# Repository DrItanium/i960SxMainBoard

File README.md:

This is the kicad project for my basic i960Sx mainboard

This is the culmination of many different designs with the most prominent being
the flattening of my internal modular board design. It was made up of mega2560
shield form factors and nucleo-144 form factor boards. It allowed me to mix and
match ideas without having to fully lay everything out over and over again. I
have no plans of releasing those designs publically because they are not
useful to anyone but myself.

This is a mini-itx board that requires a separate MightyCore development board
to plug into. This board is the culmination of years of work and design. I am
nowhere done but this is the next phase of the design

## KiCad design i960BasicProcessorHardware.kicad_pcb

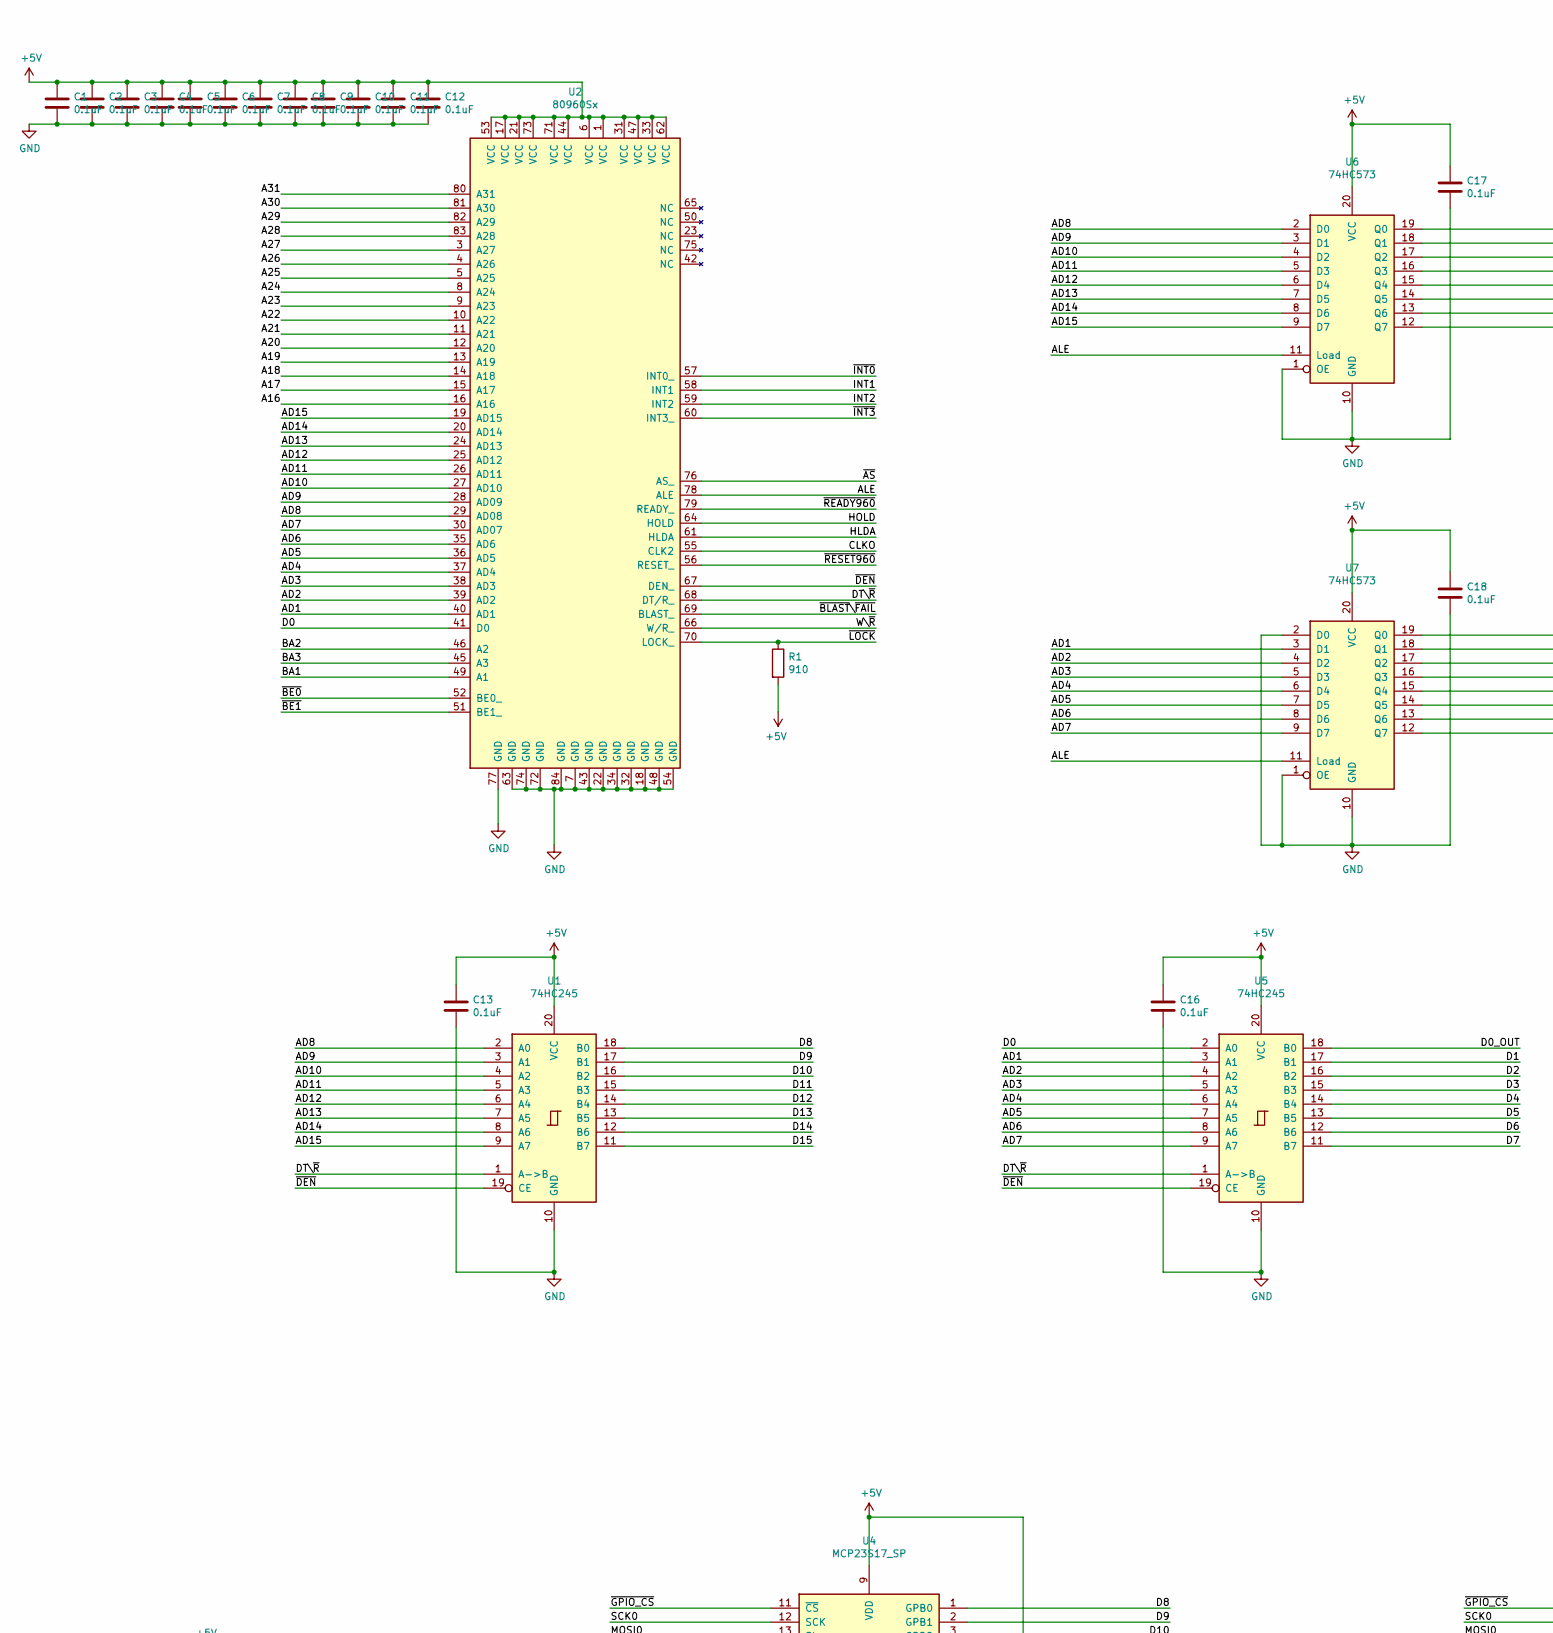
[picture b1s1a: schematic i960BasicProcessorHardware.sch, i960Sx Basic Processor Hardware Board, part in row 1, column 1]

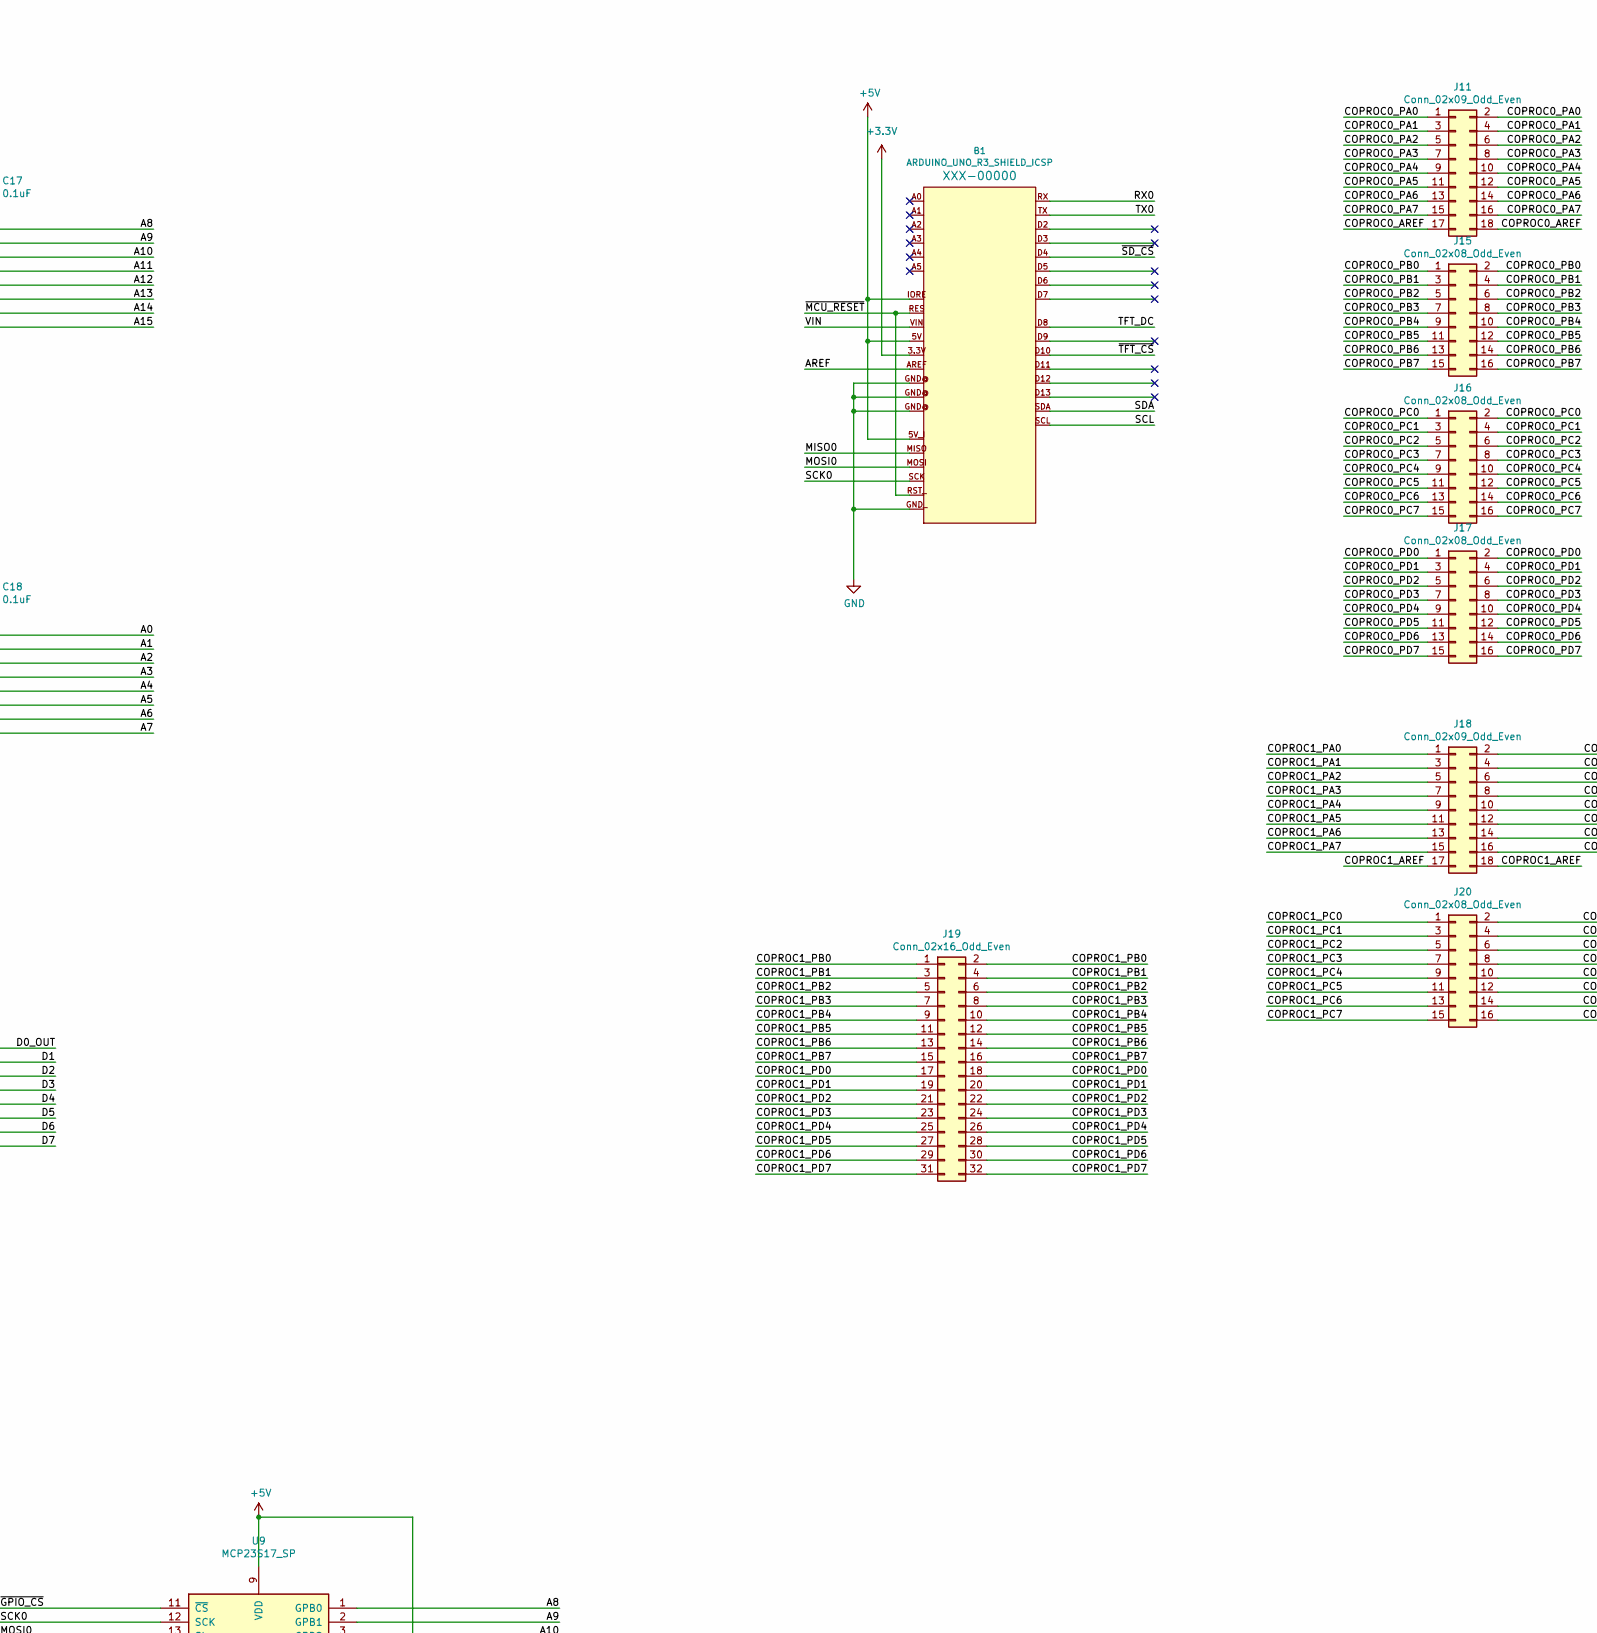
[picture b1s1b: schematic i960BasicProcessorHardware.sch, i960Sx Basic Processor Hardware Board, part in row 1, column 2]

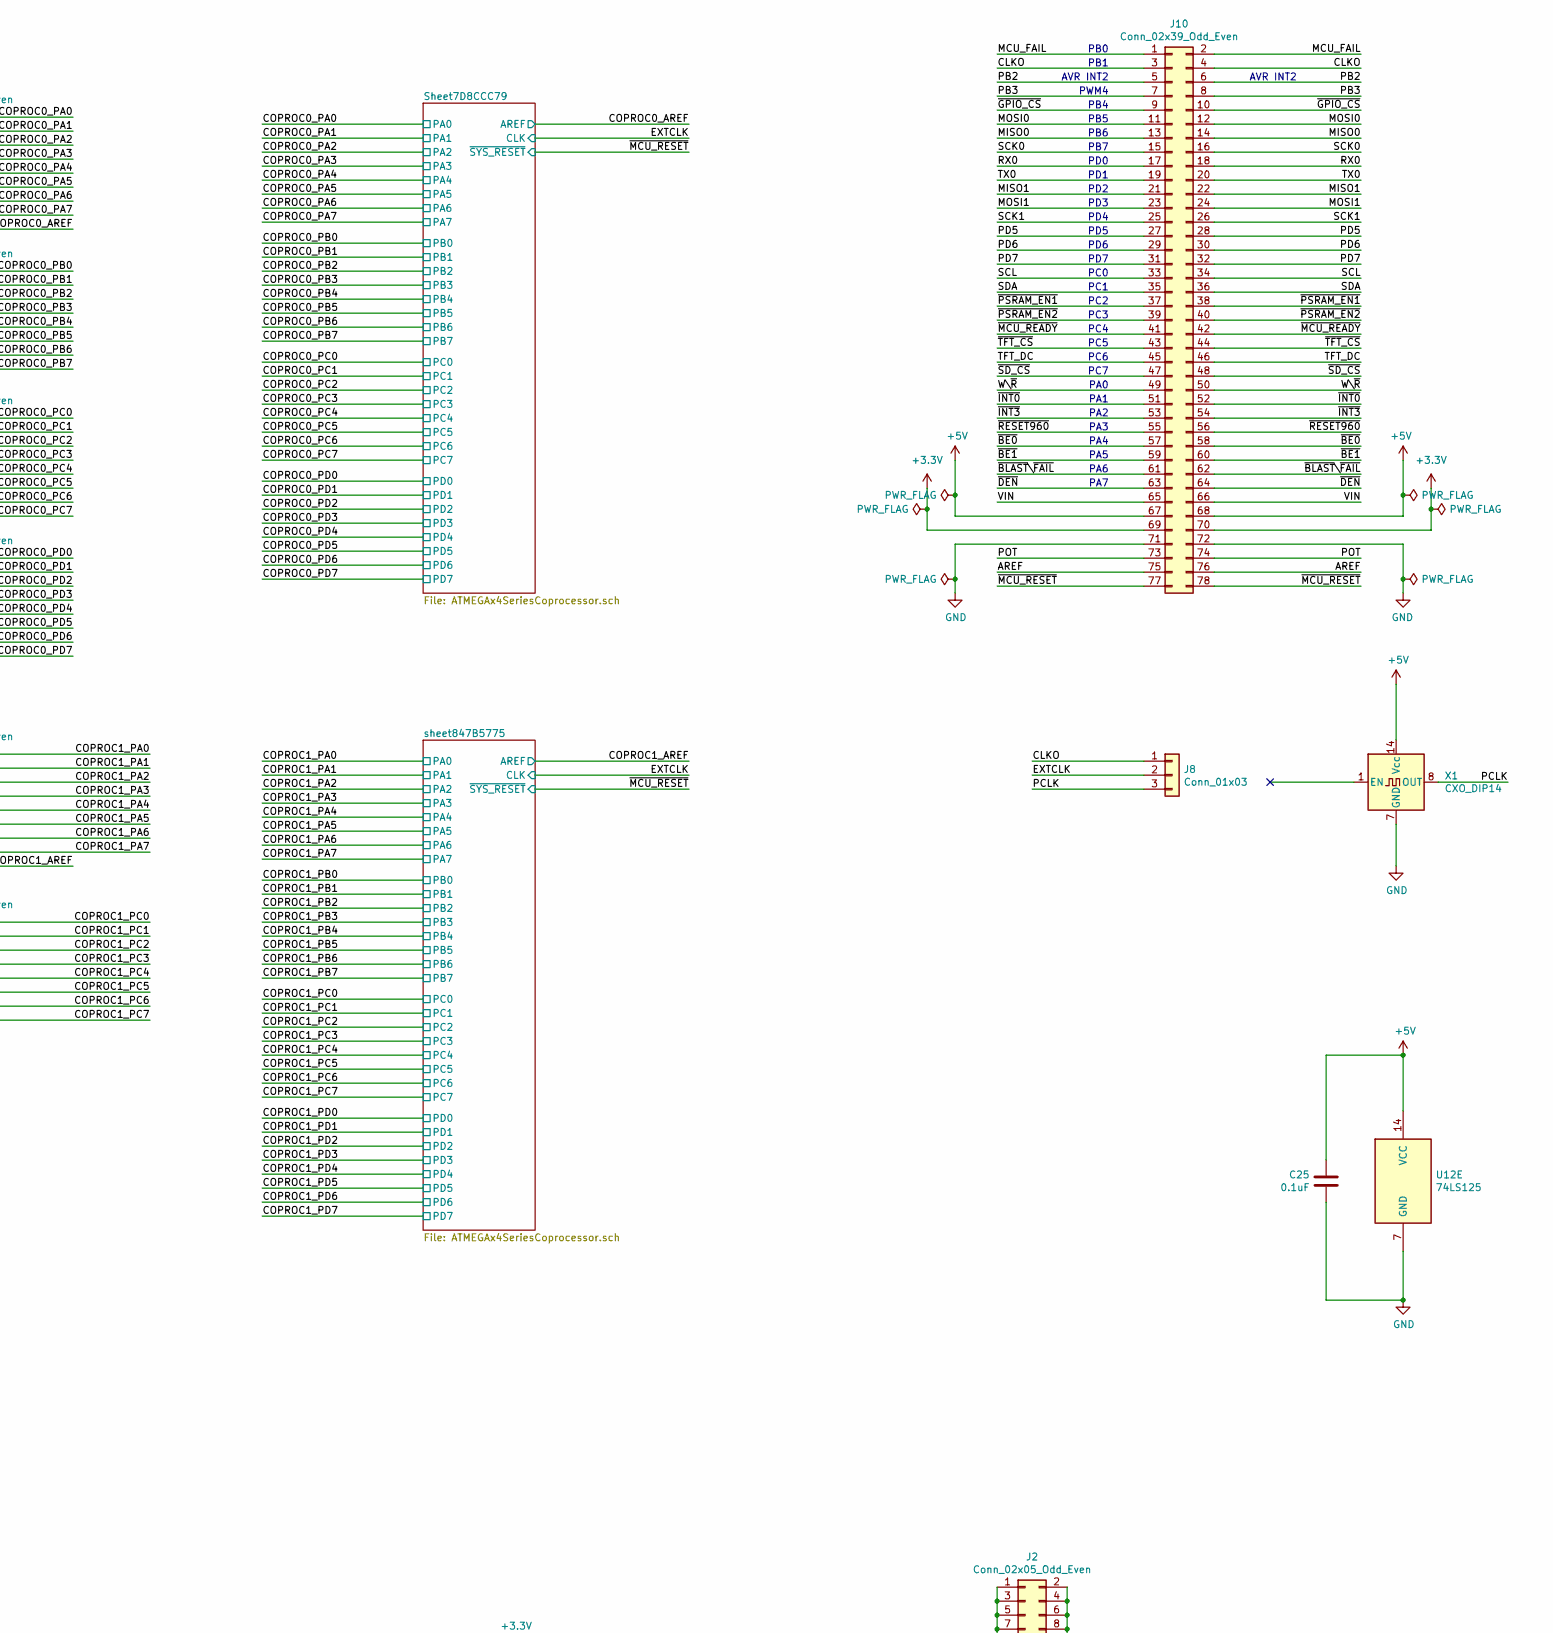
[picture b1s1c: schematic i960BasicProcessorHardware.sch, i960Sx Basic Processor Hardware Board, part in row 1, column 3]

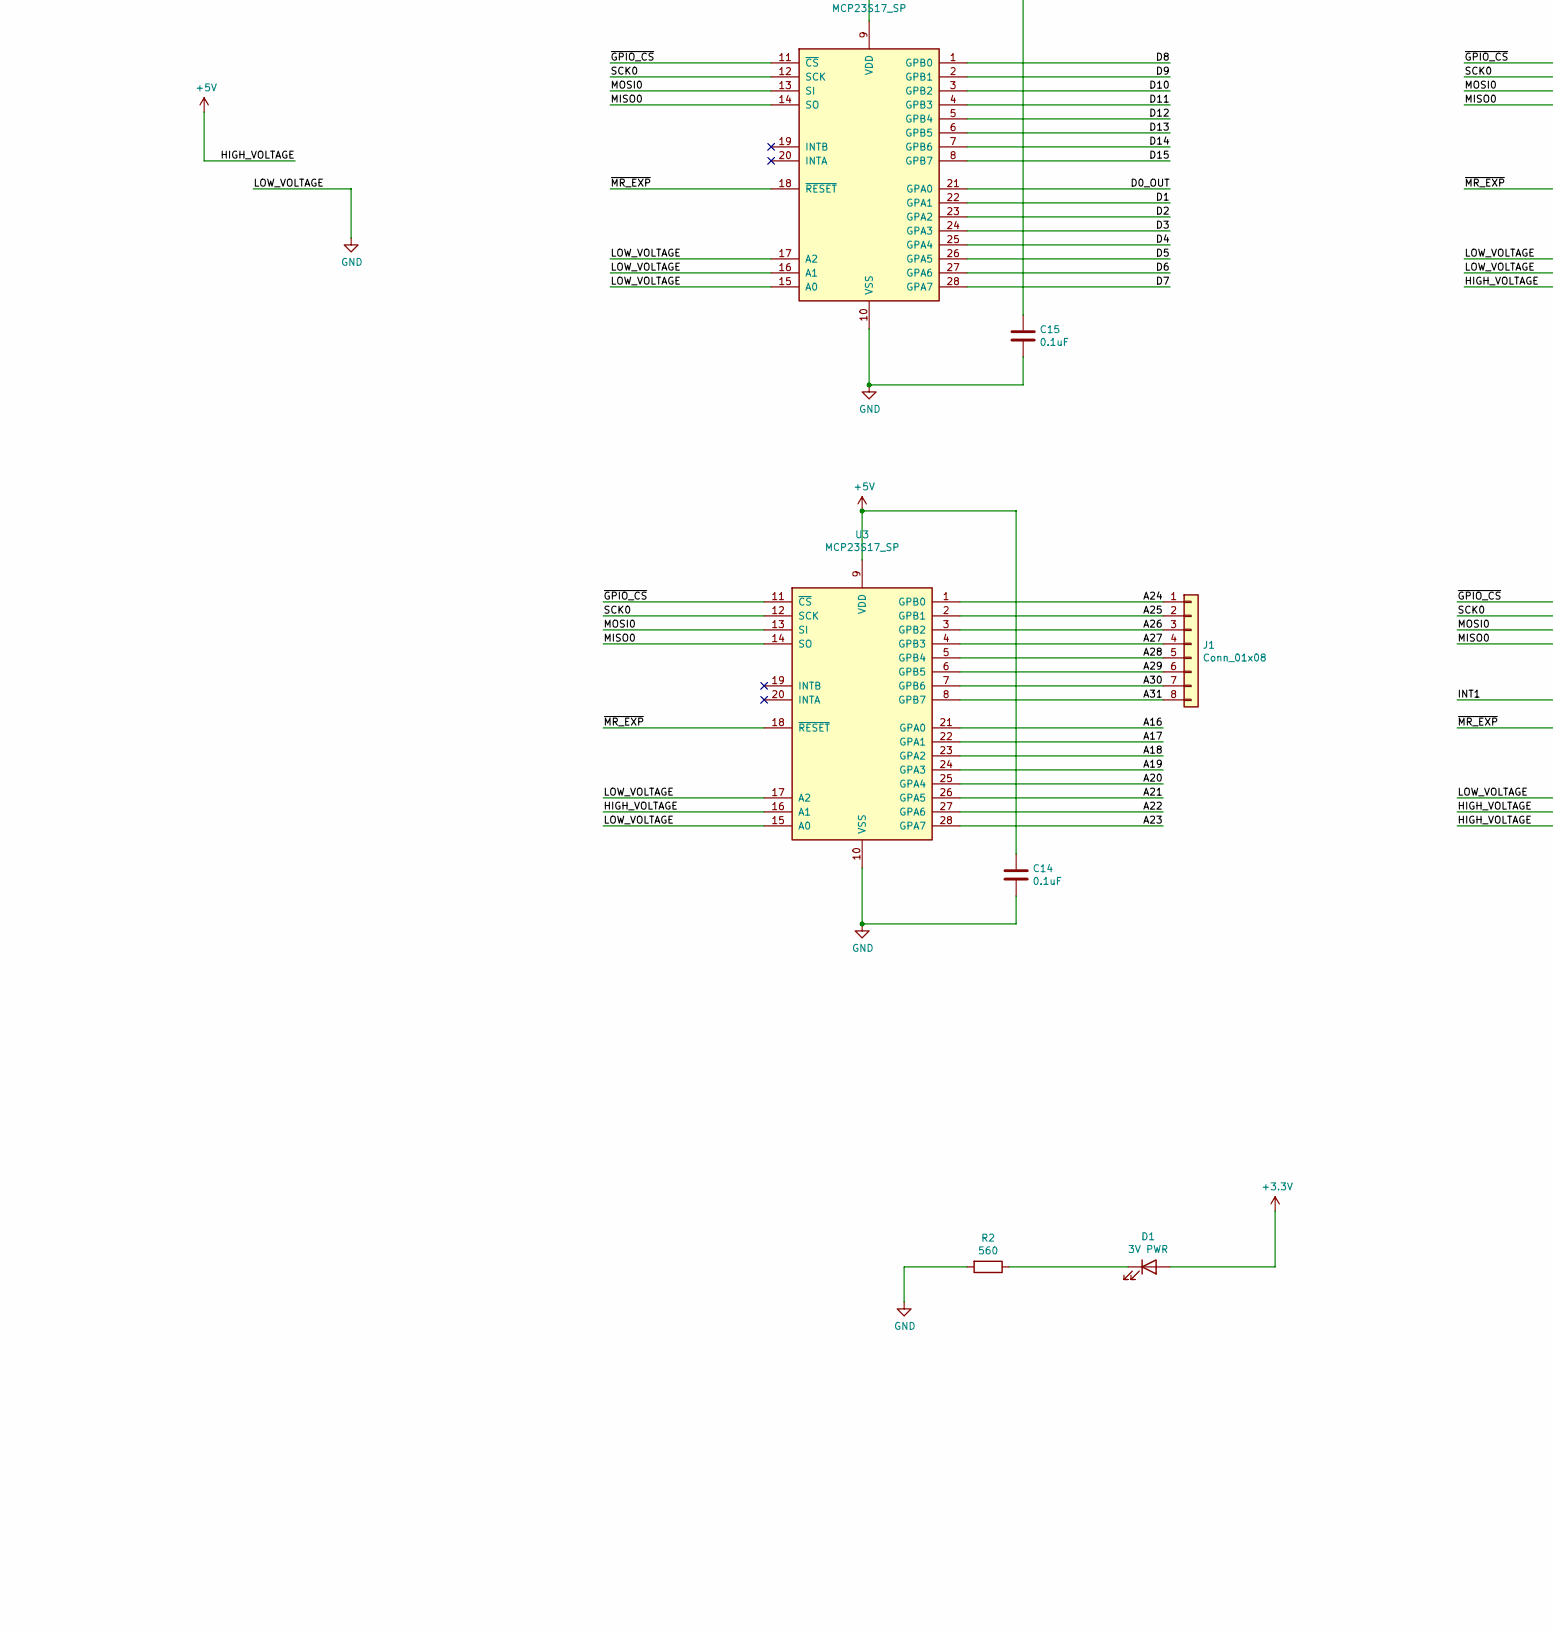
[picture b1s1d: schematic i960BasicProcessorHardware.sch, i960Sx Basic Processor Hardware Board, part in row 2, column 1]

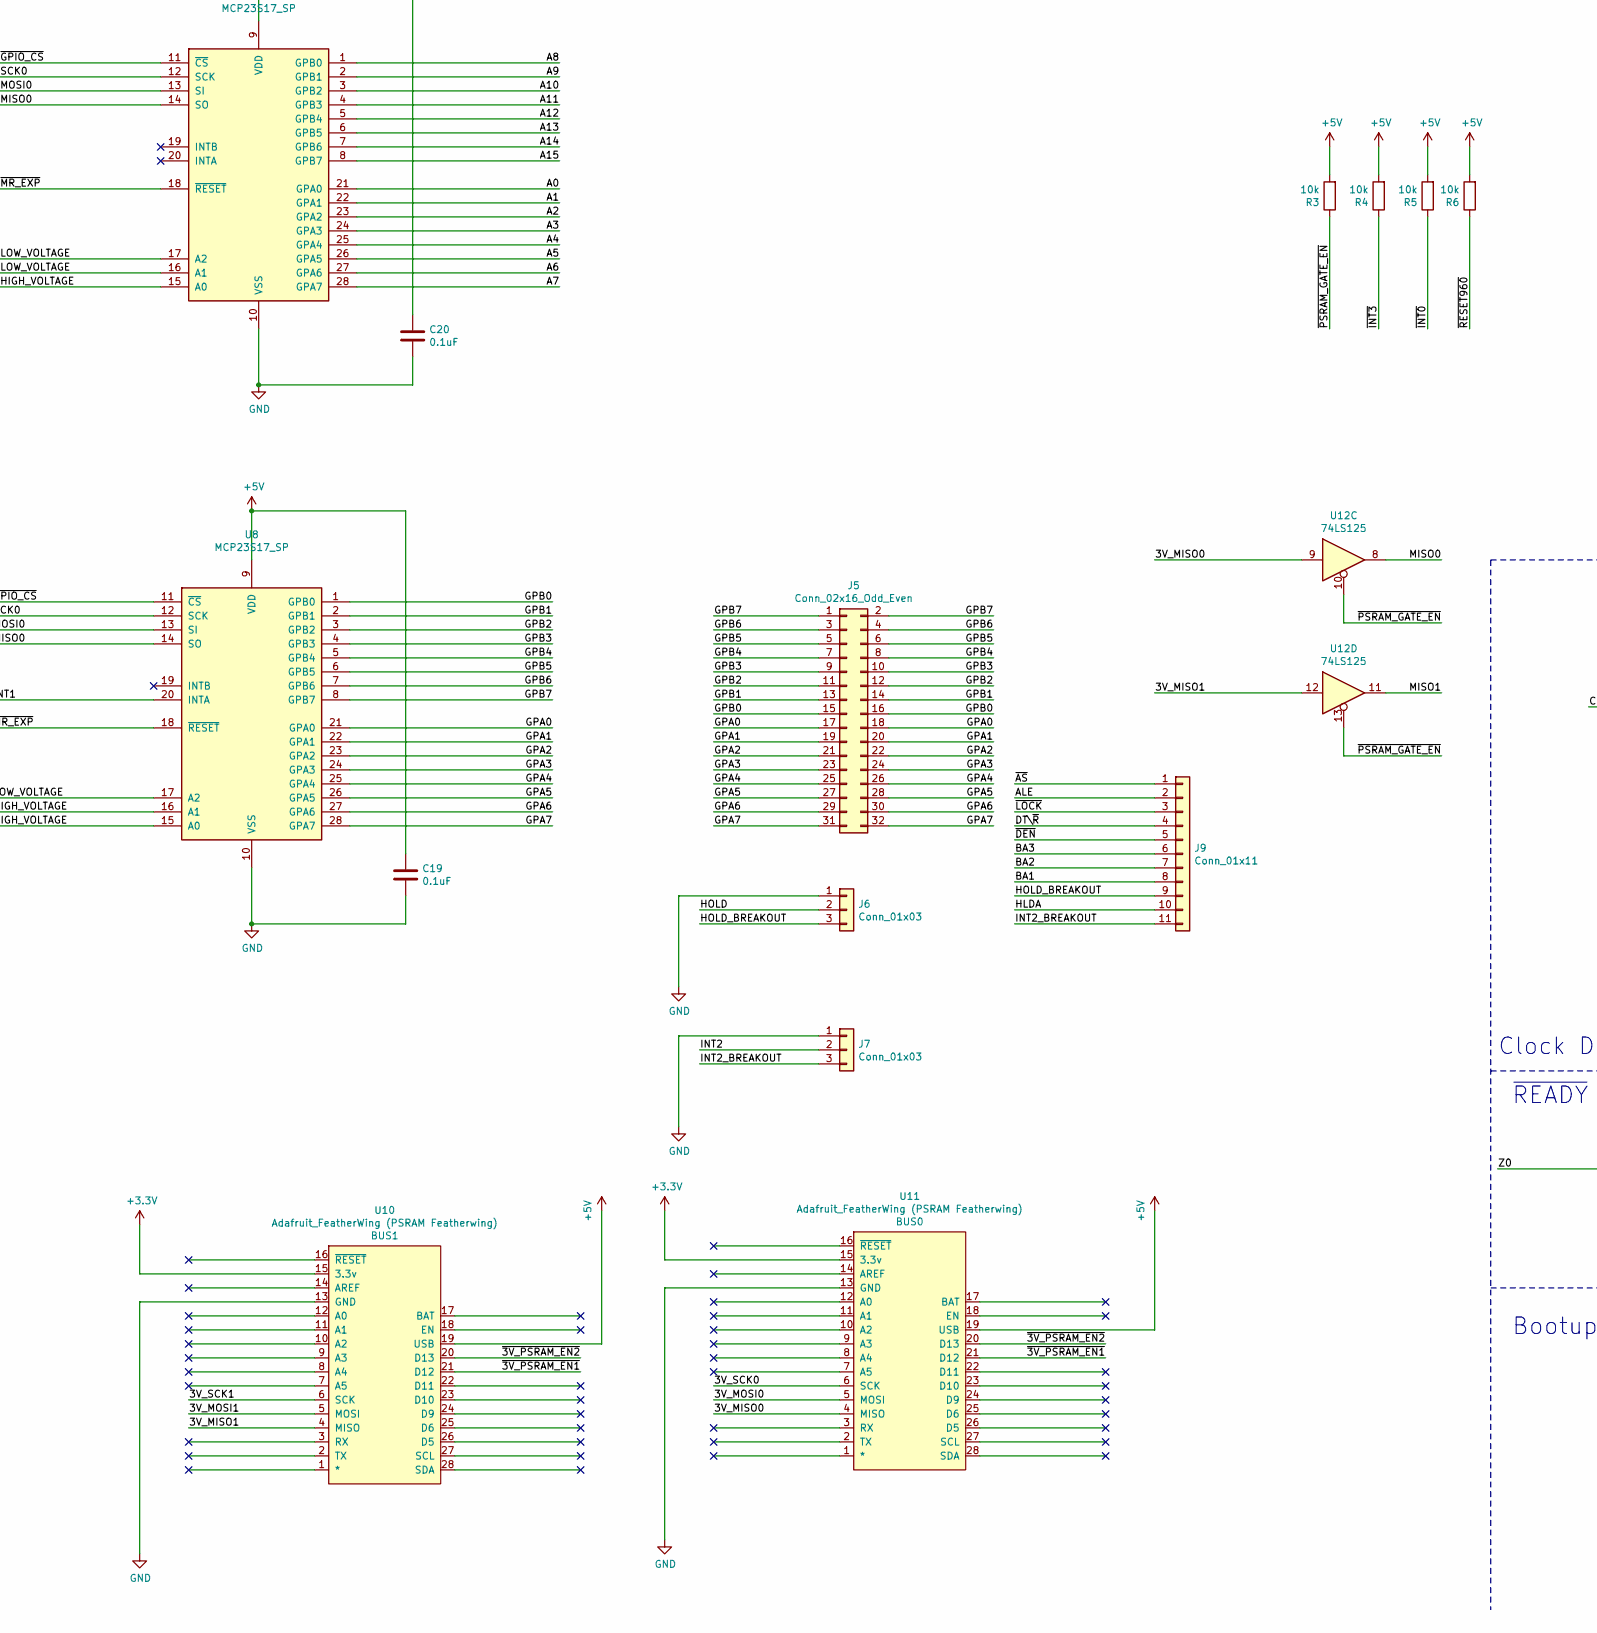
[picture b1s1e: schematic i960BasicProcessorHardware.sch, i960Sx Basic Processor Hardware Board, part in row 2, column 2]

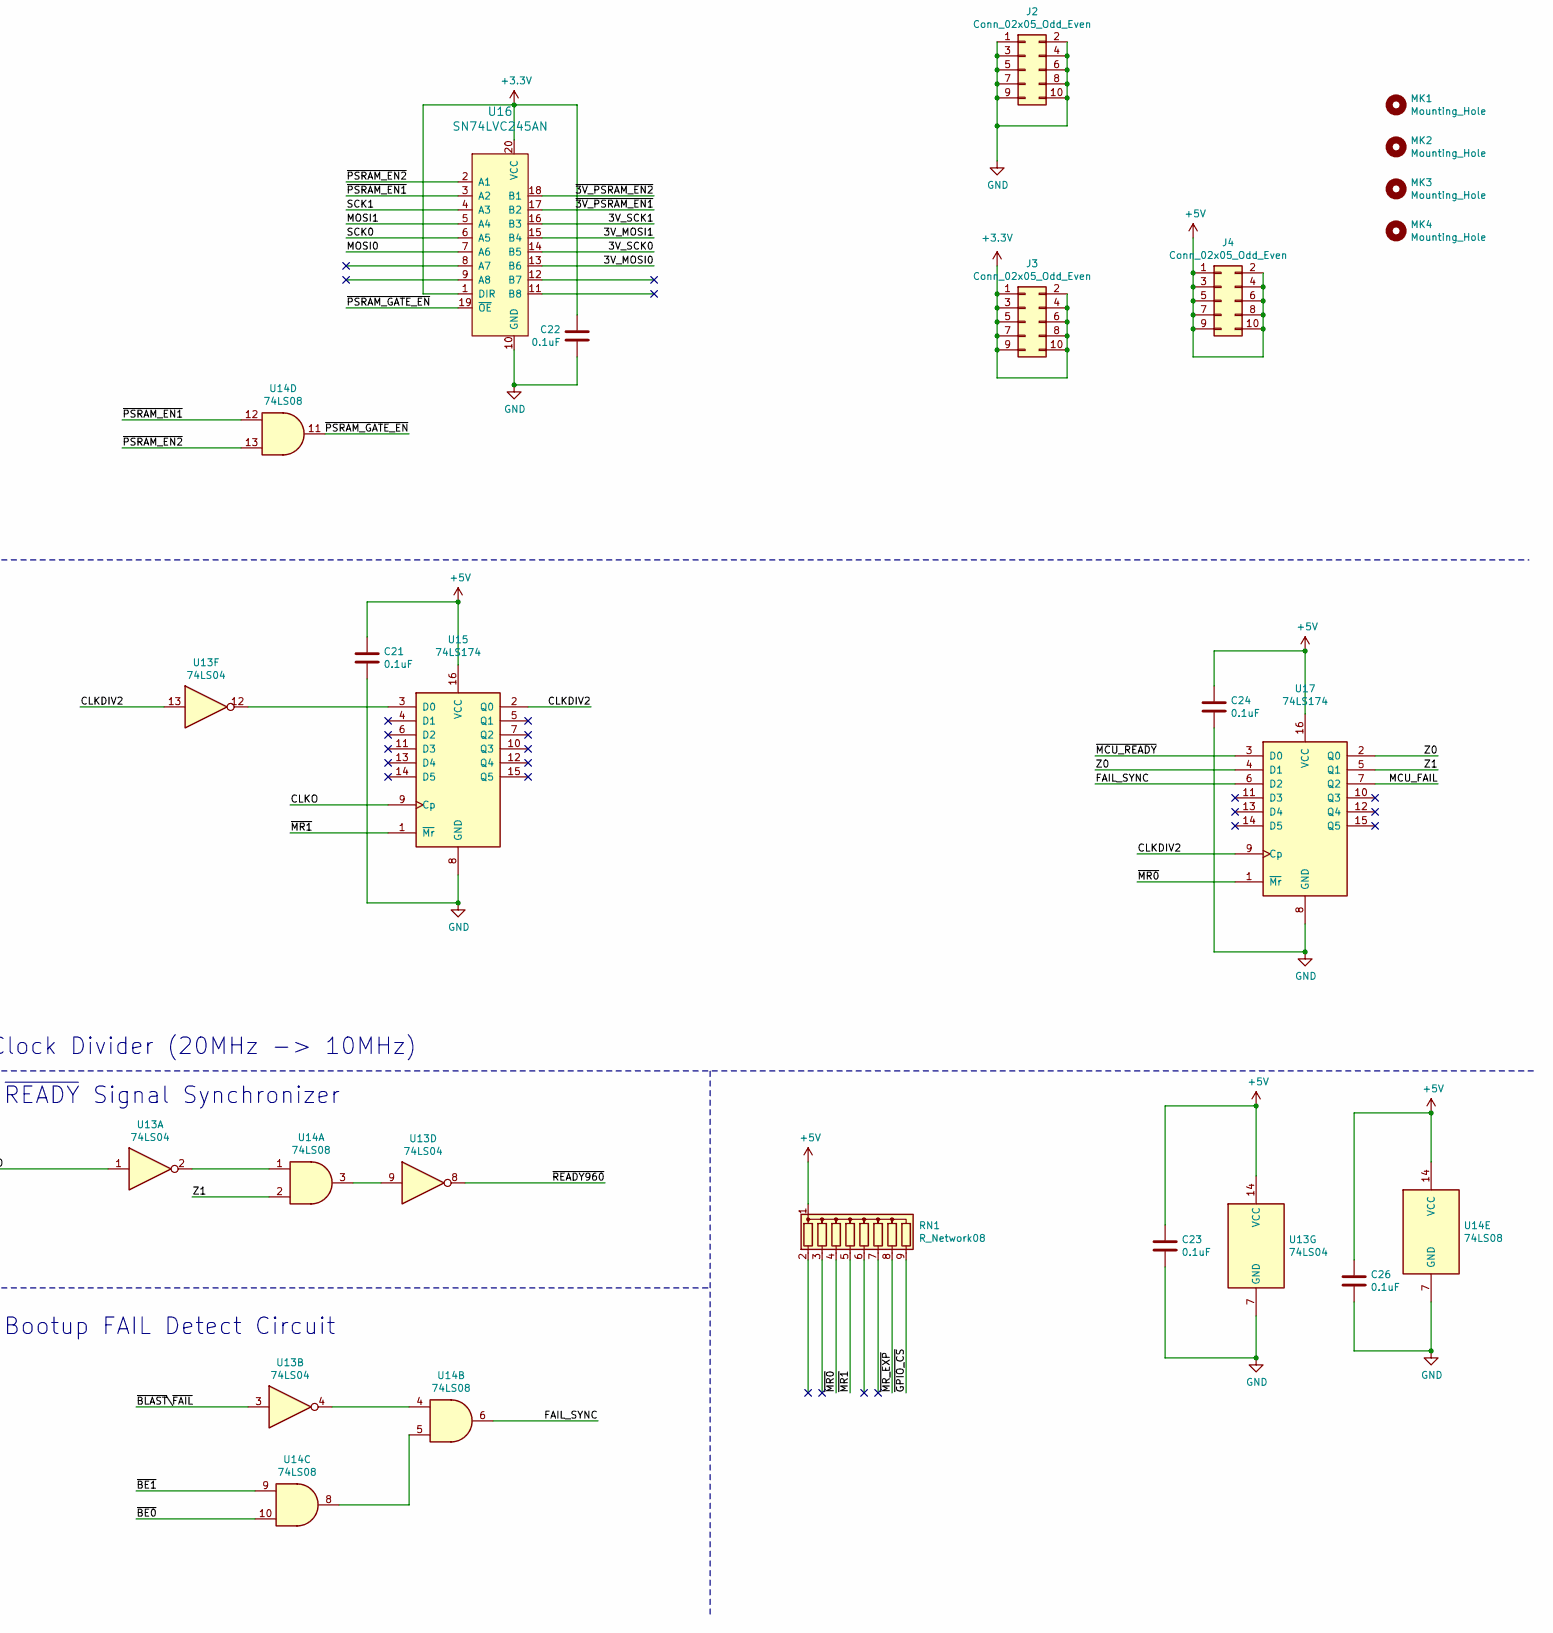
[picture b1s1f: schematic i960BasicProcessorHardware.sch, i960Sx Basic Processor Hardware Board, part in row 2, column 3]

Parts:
B1: ARDUINO_UNO_R3_SHIELD_ICSP; UNO_R3_SHIELD_ICSP
C1, C2, C3, C4, C5, C6, C7, C8, C9, C10, C11, C12, C13, C14, C15, C16, C17, C18, C19, C20, C21, C22, C23, C24, C25, C26: 0.1uF; C_0805_2012Metric_Pad1.18x1.45mm_HandSolder
D1: 3V PWR; LED_0805_2012Metric_Pad1.15x1.40mm_HandSolder
J1: Conn_01x08; PinHeader_1x08_P2.54mm_Vertical
J2, J3, J4: Conn_02x05_Odd_Even; PinHeader_2x05_P2.54mm_Vertical
J5, J19: Conn_02x16_Odd_Even; PinHeader_2x16_P2.54mm_Vertical
J6, J7, J8: Conn_01x03; PinHeader_1x03_P2.54mm_Vertical
J9: Conn_01x11; PinHeader_1x11_P2.54mm_Vertical
J10: Conn_02x39_Odd_Even; PinHeader_2x39_P2.54mm_Vertical
J11, J18: Conn_02x09_Odd_Even; PinHeader_2x09_P2.54mm_Vertical
J15, J16, J17, J20: Conn_02x08_Odd_Even; PinHeader_2x08_P2.54mm_Vertical
MK1, MK2, MK3, MK4: Mounting_Hole; MountingHole_4.3mm_M4
R1: 910; R_0805_2012Metric_Pad1.20x1.40mm_HandSolder
R2: 560; R_0805_2012Metric_Pad1.20x1.40mm_HandSolder
R3, R4, R5, R6: 10k; R_0805_2012Metric_Pad1.20x1.40mm_HandSolder
RN1: R_Network08; R_Array_SIP9
U1, U5: 74HC245; DIP-20_W7.62mm_Socket
U2: 80960Sx; PLCC-84_THT-Socket
U3, U4, U8, U9: MCP23S17_SP; DIP-28_W7.62mm
U6, U7: 74HC573; DIP-20_W7.62mm_Socket
U10, U11: Adafruit_FeatherWing (PSRAM Featherwing); ADAFRUIT_FEATHER
U12: 74LS125; DIP-14_W7.62mm_Socket
U13: 74LS04; DIP-14_W7.62mm_Socket
U14: 74LS08; DIP-14_W7.62mm_Socket
U15, U17: 74LS174; DIP-16_W7.62mm_Socket
U16: SN74LVC245AN; DIP-20_W7.62mm_Socket; MPN SN74LVC245AN; Digi-Key_PN 296-8503-5-ND
X1: CXO_DIP14; Oscillator_DIP-14

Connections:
+3V3: B1.3.3V, C22.1, D1.2 (A), J3.1, J3.2, J3.3, J3.4, J3.5, J3.6, J3.7, J3.8, J3.9, J3.10, J10.69, J10.70, U10.15 (3.3v), U11.15 (3.3v), U16.1 (DIR), U16.20 (VCC)
+5V: B1.5V, B1.5V_I (VCC), B1.IORE (IOREF), C1.1, C2.1, C3.1, C4.1, C5.1, C6.1, C7.1, C8.1, C9.1, C10.1, C11.1, C12.1, C13.1, C14.1, C15.1, C16.1, C17.1, C18.1, C19.1, C20.1, C21.1, C23.1, C24.1, C25.1, C26.1, J4.1, J4.2, J4.3, J4.4, J4.5, J4.6, J4.7, J4.8, J4.9, J4.10, J10.67, J10.68, R1.2, R3.2, R4.2, R5.2, R6.2, RN1.1 (common), U1.20 (VCC), U2.1 (VCC), U2.6 (VCC), U2.17 (VCC), U2.21 (VCC), U2.31 (VCC), U2.33 (VCC), U2.44 (VCC), U2.47 (VCC), U2.53 (VCC), U2.62 (VCC), U2.71 (VCC), U2.73 (VCC), U3.9 (VDD), U3.16 (A1), U4.9 (VDD), U5.20 (VCC), U6.20 (VCC), U7.20 (VCC), U8.9 (VDD), U8.15 (A0), U8.16 (A1), U9.9 (VDD), U9.15 (A0), U10.19 (USB), U11.19 (USB), U12.14 (VCC), U13.14 (VCC), U14.14 (VCC), U15.16 (VCC), U17.16 (VCC), X1.14 (Vcc); also elsewhere on the board
/3V_MISO0: U11.4 (MISO), U12.9
/3V_MISO1: U10.4 (MISO), U12.12
/3V_MOSI0: U11.5 (MOSI), U16.13 (B6)
/3V_MOSI1: U10.5 (MOSI), U16.15 (B4)
/3V_SCK0: U11.6 (SCK), U16.14 (B5)
/3V_SCK1: U10.6 (SCK), U16.16 (B3)
/A0: U7.19 (Q0), U9.21 (GPA0)
/A1: U7.18 (Q1), U9.22 (GPA1)
/A2: U7.17 (Q2), U9.23 (GPA2)
/A3: U7.16 (Q3), U9.24 (GPA3)
/A4: U7.15 (Q4), U9.25 (GPA4)
/A5: U7.14 (Q5), U9.26 (GPA5)
/A6: U7.13 (Q6), U9.27 (GPA6)
/A7: U7.12 (Q7), U9.28 (GPA7)
/A8: U6.19 (Q0), U9.1 (GPB0)
/A9: U6.18 (Q1), U9.2 (GPB1)
/A10: U6.17 (Q2), U9.3 (GPB2)
/A11: U6.16 (Q3), U9.4 (GPB3)
/A12: U6.15 (Q4), U9.5 (GPB4)
/A13: U6.14 (Q5), U9.6 (GPB5)
/A14: U6.13 (Q6), U9.7 (GPB6)
/A15: U6.12 (Q7), U9.8 (GPB7)
/A16: U2.16 (A16), U3.21 (GPA0)
/A17: U2.15 (A17), U3.22 (GPA1)
/A18: U2.14 (A18), U3.23 (GPA2)
/A19: U2.13 (A19), U3.24 (GPA3)
/A20: U2.12 (A20), U3.25 (GPA4)
/A21: U2.11 (A21), U3.26 (GPA5)
/A22: U2.10 (A22), U3.27 (GPA6)
/A23: U2.9 (A23), U3.28 (GPA7)
/A24: J1.1, U2.8 (A24), U3.1 (GPB0)
/A25: J1.2, U2.5 (A25), U3.2 (GPB1)
/A26: J1.3, U2.4 (A26), U3.3 (GPB2)
/A27: J1.4, U2.3 (A27), U3.4 (GPB3)
/A28: J1.5, U2.83 (A28), U3.5 (GPB4)
/A29: J1.6, U2.82 (A29), U3.6 (GPB5)
/A30: J1.7, U2.81 (A30), U3.7 (GPB6)
/A31: J1.8, U2.80 (A31), U3.8 (GPB7)
/AD1: U2.40 (AD1), U5.3 (A1), U7.3 (D1)
/AD2: U2.39 (AD2), U5.4 (A2), U7.4 (D2)
/AD3: U2.38 (AD3), U5.5 (A3), U7.5 (D3)
/AD4: U2.37 (AD4), U5.6 (A4), U7.6 (D4)
/AD5: U2.36 (AD5), U5.7 (A5), U7.7 (D5)
/AD6: U2.35 (AD6), U5.8 (A6), U7.8 (D6)
/AD7: U2.30 (AD07), U5.9 (A7), U7.9 (D7)
/AD8: U1.2 (A0), U2.29 (AD08), U6.2 (D0)
/AD9: U1.3 (A1), U2.28 (AD09), U6.3 (D1)
/AD10: U1.4 (A2), U2.27 (AD10), U6.4 (D2)
/AD11: U1.5 (A3), U2.26 (AD11), U6.5 (D3)
/AD12: U1.6 (A4), U2.25 (AD12), U6.6 (D4)
/AD13: U1.7 (A5), U2.24 (AD13), U6.7 (D5)
/AD14: U1.8 (A6), U2.20 (AD14), U6.8 (D6)
/AD15: U1.9 (A7), U2.19 (AD15), U6.9 (D7)
/ALE: J9.2, U2.78 (ALE), U6.11 (Load), U7.11 (Load)
/AREF: B1.AREF, J10.75, J10.76
/BA1: J9.8, U2.49 (A1)
/BA2: J9.7, U2.46 (A2)
/BA3: J9.6, U2.45 (A3)
/CLKDIV2: U13.13, U15.2 (Q0), U17.9 (Cp)
/CLKO: J8.1, J10.3, J10.4, U2.55 (CLK2), U15.9 (Cp)
/COPROC0_AREF: J11.17, J11.18; also elsewhere on the board
/COPROC0_PA0: J11.1, J11.2; also elsewhere on the board
/COPROC0_PA1: J11.3, J11.4; also elsewhere on the board
/COPROC0_PA2: J11.5, J11.6; also elsewhere on the board
/COPROC0_PA3: J11.7, J11.8; also elsewhere on the board
/COPROC0_PA4: J11.9, J11.10; also elsewhere on the board
/COPROC0_PA5: J11.11, J11.12; also elsewhere on the board
/COPROC0_PA6: J11.13, J11.14; also elsewhere on the board
/COPROC0_PA7: J11.15, J11.16; also elsewhere on the board
/COPROC0_PB0: J15.1, J15.2; also elsewhere on the board
/COPROC0_PB1: J15.3, J15.4; also elsewhere on the board
/COPROC0_PB2: J15.5, J15.6; also elsewhere on the board
/COPROC0_PB3: J15.7, J15.8; also elsewhere on the board
/COPROC0_PB4: J15.9, J15.10; also elsewhere on the board
/COPROC0_PB5: J15.11, J15.12; also elsewhere on the board
/COPROC0_PB6: J15.13, J15.14; also elsewhere on the board
/COPROC0_PB7: J15.15, J15.16; also elsewhere on the board
/COPROC0_PC0: J16.1, J16.2; also elsewhere on the board
/COPROC0_PC1: J16.3, J16.4; also elsewhere on the board
/COPROC0_PC2: J16.5, J16.6; also elsewhere on the board
/COPROC0_PC3: J16.7, J16.8; also elsewhere on the board
/COPROC0_PC4: J16.9, J16.10; also elsewhere on the board
/COPROC0_PC5: J16.11, J16.12; also elsewhere on the board
/COPROC0_PC6: J16.13, J16.14; also elsewhere on the board
/COPROC0_PC7: J16.15, J16.16; also elsewhere on the board
/COPROC0_PD0: J17.1, J17.2; also elsewhere on the board
/COPROC0_PD1: J17.3, J17.4; also elsewhere on the board
/COPROC0_PD2: J17.5, J17.6; also elsewhere on the board
/COPROC0_PD3: J17.7, J17.8; also elsewhere on the board
/COPROC0_PD4: J17.9, J17.10; also elsewhere on the board
/COPROC0_PD5: J17.11, J17.12; also elsewhere on the board
/COPROC0_PD6: J17.13, J17.14; also elsewhere on the board
/COPROC0_PD7: J17.15, J17.16; also elsewhere on the board
/COPROC1_AREF: J18.17, J18.18; also elsewhere on the board
/COPROC1_PA0: J18.1, J18.2; also elsewhere on the board
/COPROC1_PA1: J18.3, J18.4; also elsewhere on the board
/COPROC1_PA2: J18.5, J18.6; also elsewhere on the board
/COPROC1_PA3: J18.7, J18.8; also elsewhere on the board
/COPROC1_PA4: J18.9, J18.10; also elsewhere on the board
/COPROC1_PA5: J18.11, J18.12; also elsewhere on the board
/COPROC1_PA6: J18.13, J18.14; also elsewhere on the board
/COPROC1_PA7: J18.15, J18.16; also elsewhere on the board
/COPROC1_PB0: J19.1, J19.2; also elsewhere on the board
/COPROC1_PB1: J19.3, J19.4; also elsewhere on the board
/COPROC1_PB2: J19.5, J19.6; also elsewhere on the board
/COPROC1_PB3: J19.7, J19.8; also elsewhere on the board
/COPROC1_PB4: J19.9, J19.10; also elsewhere on the board
/COPROC1_PB5: J19.11, J19.12; also elsewhere on the board
/COPROC1_PB6: J19.13, J19.14; also elsewhere on the board
/COPROC1_PB7: J19.15, J19.16; also elsewhere on the board
/COPROC1_PC0: J20.1, J20.2; also elsewhere on the board
/COPROC1_PC1: J20.3, J20.4; also elsewhere on the board
/COPROC1_PC2: J20.5, J20.6; also elsewhere on the board
/COPROC1_PC3: J20.7, J20.8; also elsewhere on the board
/COPROC1_PC4: J20.9, J20.10; also elsewhere on the board
/COPROC1_PC5: J20.11, J20.12; also elsewhere on the board
/COPROC1_PC6: J20.13, J20.14; also elsewhere on the board
/COPROC1_PC7: J20.15, J20.16; also elsewhere on the board
/COPROC1_PD0: J19.17, J19.18; also elsewhere on the board
/COPROC1_PD1: J19.19, J19.20; also elsewhere on the board
/COPROC1_PD2: J19.21, J19.22; also elsewhere on the board
/COPROC1_PD3: J19.23, J19.24; also elsewhere on the board
/COPROC1_PD4: J19.25, J19.26; also elsewhere on the board
/COPROC1_PD5: J19.27, J19.28; also elsewhere on the board
/COPROC1_PD6: J19.29, J19.30; also elsewhere on the board
/COPROC1_PD7: J19.31, J19.32; also elsewhere on the board
/D0: U2.41 (D0), U5.2 (A0)
/D0_OUT: U4.21 (GPA0), U5.18 (B0)
/D1: U4.22 (GPA1), U5.17 (B1)
/D2: U4.23 (GPA2), U5.16 (B2)
/D3: U4.24 (GPA3), U5.15 (B3)
/D4: U4.25 (GPA4), U5.14 (B4)
/D5: U4.26 (GPA5), U5.13 (B5)
/D6: U4.27 (GPA6), U5.12 (B6)
/D7: U4.28 (GPA7), U5.11 (B7)
/D8: U1.18 (B0), U4.1 (GPB0)
/D9: U1.17 (B1), U4.2 (GPB1)
/D10: U1.16 (B2), U4.3 (GPB2)
/D11: U1.15 (B3), U4.4 (GPB3)
/D12: U1.14 (B4), U4.5 (GPB4)
/D13: U1.13 (B5), U4.6 (GPB5)
/D14: U1.12 (B6), U4.7 (GPB6)
/D15: U1.11 (B7), U4.8 (GPB7)
/DT\~R: J9.4, U1.1 (A->B), U2.68 (DT/R_), U5.1 (A->B)
/EXTCLK: J8.2; also elsewhere on the board
/FAIL_SYNC: U14.6, U17.6 (D2)
/GPA0: J5.17, J5.18, U8.21 (GPA0)
/GPA1: J5.19, J5.20, U8.22 (GPA1)
/GPA2: J5.21, J5.22, U8.23 (GPA2)
/GPA3: J5.23, J5.24, U8.24 (GPA3)
/GPA4: J5.25, J5.26, U8.25 (GPA4)
/GPA5: J5.27, J5.28, U8.26 (GPA5)
/GPA6: J5.29, J5.30, U8.27 (GPA6)
/GPA7: J5.31, J5.32, U8.28 (GPA7)
/GPB0: J5.15, J5.16, U8.1 (GPB0)
/GPB1: J5.13, J5.14, U8.2 (GPB1)
/GPB2: J5.11, J5.12, U8.3 (GPB2)
/GPB3: J5.9, J5.10, U8.4 (GPB3)
/GPB4: J5.7, J5.8, U8.5 (GPB4)
/GPB5: J5.5, J5.6, U8.6 (GPB5)
/GPB6: J5.3, J5.4, U8.7 (GPB6)
/GPB7: J5.1, J5.2, U8.8 (GPB7)
/HLDA: J9.10, U2.61 (HLDA)
/HOLD: J6.2, U2.64 (HOLD)
/HOLD_BREAKOUT: J6.3, J9.9
/INT1: U2.58 (INT1), U8.20 (INTA)
/INT2: J7.2, U2.59 (INT2)
/INT2_BREAKOUT: J7.3, J9.11
/MCU_FAIL: J10.1, J10.2, U17.7 (Q2)
/MISO0: B1.MISO, J10.13, J10.14, U3.14 (SO), U4.14 (SO), U8.14 (SO), U9.14 (SO), U12.8
/MISO1: J10.21, J10.22, U12.11
/MOSI0: B1.MOSI, J10.11, J10.12, U3.13 (SI), U4.13 (SI), U8.13 (SI), U9.13 (SI), U16.7 (A6)
/MOSI1: J10.23, J10.24, U16.5 (A4)
/PB2: J10.5, J10.6
/PB3: J10.7, J10.8
/PCLK: J8.3, X1.8 (OUT)
/PD5: J10.27, J10.28
/PD6: J10.29, J10.30
/PD7: J10.31, J10.32
/POT: J10.73, J10.74
/RX0: B1.RX (D0), J10.17, J10.18
/SCK0: B1.SCK, J10.15, J10.16, U3.12 (SCK), U4.12 (SCK), U8.12 (SCK), U9.12 (SCK), U16.6 (A5)
/SCK1: J10.25, J10.26, U16.4 (A3)
/SCL: B1.SCL, J10.33, J10.34
/SDA: B1.SDA, J10.35, J10.36
/TFT_DC: B1.D8, J10.45, J10.46
/TX0: B1.TX (D1), J10.19, J10.20
/VIN: B1.VIN, J10.65, J10.66
/W\~R~: J10.49, J10.50, U2.66 (W/R_)
/Z0: U13.1, U17.2 (Q0), U17.4 (D1)
/Z1: U14.2, U17.5 (Q1)
/~3V_PSRAM_EN1: U10.21 (D12), U11.21 (D12), U16.17 (B2)
/~3V_PSRAM_EN2: U10.20 (D13), U11.20 (D13), U16.18 (B1)
/~AS: J9.1, U2.76 (AS_)
/~BE0: J10.57, J10.58, U2.52 (BE0_), U14.10
/~BE1: J10.59, J10.60, U2.51 (BE1_), U14.9
/~BLAST~\~FAIL~: J10.61, J10.62, U2.69 (BLAST_), U13.3
/~DEN: J9.5, J10.63, J10.64, U1.19 (CE), U2.67 (DEN_), U5.19 (CE)
/~GPIO_CS: J10.9, J10.10, RN1.9 (R8), U3.11 (~CS~), U4.11 (~CS~), U8.11 (~CS~), U9.11 (~CS~)
/~INT0: J10.51, J10.52, R5.1, U2.57 (INT0_)
/~INT3: J10.53, J10.54, R4.1, U2.60 (INT3_)
/~LOCK: J9.3, R1.1, U2.70 (LOCK_)
/~MCU_READY: J10.41, J10.42, U17.3 (D0)
/~MCU_RESET: B1.RES (~RESET~), B1.RST_ (~RESET~), J10.77, J10.78; also elsewhere on the board
/~MR0: RN1.4 (R3), U17.1 (~Mr)
/~MR1: RN1.5 (R4), U15.1 (~Mr)
/~MR_EXP: RN1.8 (R7), U3.18 (~RESET~), U4.18 (~RESET~), U8.18 (~RESET~), U9.18 (~RESET~)
/~PSRAM_EN1: J10.37, J10.38, U14.12, U16.3 (A2)
/~PSRAM_EN2: J10.39, J10.40, U14.13, U16.2 (A1)
/~PSRAM_GATE_EN: R3.1, U12.10, U12.13, U14.11, U16.19 (~OE)
/~READY960: U2.79 (READY_), U13.8
/~RESET960: J10.55, J10.56, R6.1, U2.56 (RESET_)
/~SD_CS: B1.D4, J10.47, J10.48
/~TFT_CS: B1.D10 (*D10), J10.43, J10.44
GND: B1.GND@ (GND), B1.GND_ (GND), C1.2, C2.2, C3.2, C4.2, C5.2, C6.2, C7.2, C8.2, C9.2, C10.2, C11.2, C12.2, C13.2, C14.2, C15.2, C16.2, C17.2, C18.2, C19.2, C20.2, C21.2, C22.2, C23.2, C24.2, C25.2, C26.2, J2.1, J2.2, J2.3, J2.4, J2.5, J2.6, J2.7, J2.8, J2.9, J2.10, J6.1, J7.1, J10.71, J10.72, R2.2, U1.10 (GND), U2.7 (GND), U2.18 (GND), U2.22 (GND), U2.32 (GND), U2.34 (GND), U2.43 (GND), U2.48 (GND), U2.54 (GND), U2.63 (GND), U2.72 (GND), U2.74 (GND), U2.77 (GND), U2.84 (GND), U3.10 (VSS), U3.15 (A0), U3.17 (A2), U4.10 (VSS), U4.15 (A0), U4.16 (A1), U4.17 (A2), U5.10 (GND), U6.1 (OE), U6.10 (GND), U7.1 (OE), U7.2 (D0), U7.10 (GND), U8.10 (VSS), U8.17 (A2), U9.10 (VSS), U9.16 (A1), U9.17 (A2), U10.13 (GND), U11.13 (GND), U12.7 (GND), U13.7 (GND), U14.7 (GND), U15.8 (GND), U16.10 (GND), U17.8 (GND), X1.7 (GND); also elsewhere on the board
unnamed: D1.1 (K), R2.1
unnamed: U13.2, U14.1
unnamed: U13.4, U14.4
unnamed: U13.9, U14.3
unnamed: U13.12, U15.3 (D0)
unnamed: U14.5, U14.8

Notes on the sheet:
Bootup FAIL Detect Circuit
Clock Divider (20MHz -> 10MHz)
~READY~ Signal Synchronizer
PB0
PB1
PWM4
PB4
PB5
PB6
PB7
PD0
PD1
PD2
PD3
PD4
PD5
PD6
PD7
PC0
PC1
PC2
PC3
PC4
PC5
PC6
PC7
PA0
PA1
PA2
PA3
PA4
PA5
PA6
PA7
AVR INT2

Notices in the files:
i960BasicProcessorHardware.kicad_pcb:
(C) 2021 Joshua Scoggins
